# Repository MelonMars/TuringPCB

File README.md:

# Turing PCB

This is a PCB for a [Turing Machine](https://en.wikipedia.org/wiki/Turing_machine) that is made primarily using "simple" components, without using complex microchips or programmable stuff (as that would be cheating). It is designed to be programmed through the transition table being bridged by diodes (e.g. LEDs) in order to represent what is being done and how the machine should progress. It has both an automatic clock and the ability to step through it, to enable debugging programs or just run through them. It has 4 state bits and 8 tape bits. It ended up being much more complex than I thought at first, and took way longer than expected, but it was really enjoyable. It has 6 layers & 2 flood fills for both GND and VCC.

I made this project primarily for the fun of it. I've always found challenges with confounding variables fun and interesting, and believe that this is just sort of the next step in that regard, with Turing Machine's being fun proofs of concept and this being a very restricted form of it.

Bill of materials:
1x PCB (JLCPCB) -- $62.70

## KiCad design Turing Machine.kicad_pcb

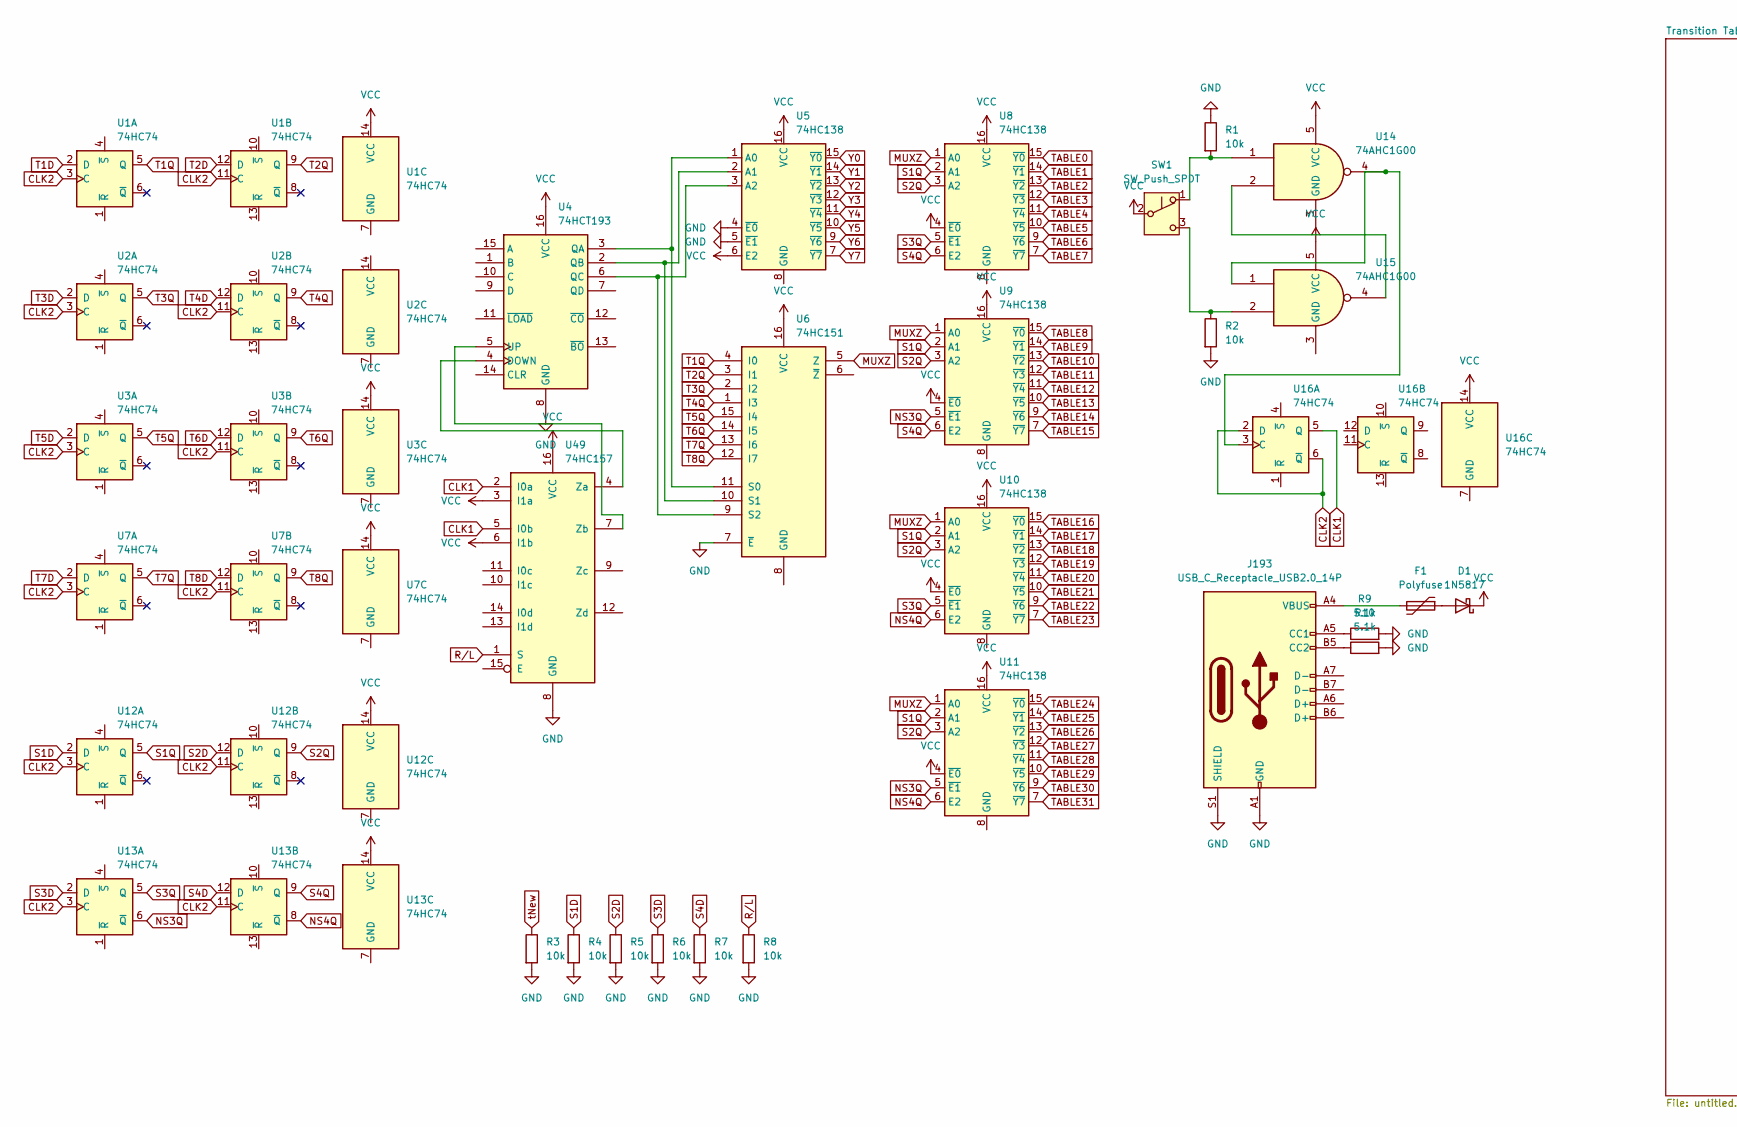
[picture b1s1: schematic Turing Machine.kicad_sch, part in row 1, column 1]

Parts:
D1: 1N5817; D_DO-41_SOD81_P10.16mm_Horizontal
F1: Polyfuse; Fuse_1812_4532Metric
J193: USB_C_Receptacle_USB2.0_14P; USB_C_Receptacle_GCT_USB4085
R1, R2, R3, R4, R5, R6, R7, R8: 10k; R_0603_1608Metric
R9, R10: 5.1k; R_0603_1608Metric
SW1: SW_Push_SPDT; Nidec_Copal_CAS-120A
U1, U2, U3, U7, U12, U13, U16: 74HC74; SOIC-14_3.9x8.7mm_P1.27mm
U4: 74HCT193; SOIC-16_3.9x9.9mm_P1.27mm
U5, U8, U9, U10, U11: 74HC138; SOIC-16_3.9x9.9mm_P1.27mm
U6: 74HC151; SOIC-16_3.9x9.9mm_P1.27mm
U14, U15: 74AHC1G00; SOT-23-5
U49: 74HC157; SOIC-16_3.9x9.9mm_P1.27mm

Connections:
CLK1: U16.5 (Q), U49.2 (I0a), U49.5 (I0b)
CLK2: U1.3 (C), U1.11 (C), U2.3 (C), U2.11 (C), U3.3 (C), U3.11 (C), U7.3 (C), U7.11 (C), U12.3 (C), U12.11 (C), U13.3 (C), U13.11 (C), U16.2 (D), U16.6 (~Q)
GND: J193.A1 (GND), J193.A12 (GND), J193.B1 (GND), J193.B12 (GND), J193.S1 (SHIELD), R1.1, R2.2, R3.2, R4.2, R5.2, R6.2, R7.2, R8.2, R9.2, R10.2, U4.8 (GND), U5.4 (~E0), U5.5 (~E1), U6.7 (~E), U49.8 (GND); also elsewhere on the board
MUXZ: U6.5 (Z), U8.1 (A0), U9.1 (A0), U10.1 (A0), U11.1 (A0)
NS3Q: U9.5 (~E1), U11.5 (~E1), U13.6 (~Q)
NS4Q: U10.6 (E2), U11.6 (E2), U13.8 (~Q)
unnamed: D1.2 (A), F1.1
unnamed: F1.2, J193.A4 (VBUS), J193.A9 (VBUS), J193.B4 (VBUS), J193.B9 (VBUS)
unnamed: J193.A5 (CC1), R9.1
unnamed: J193.B5 (CC2), R10.1
unnamed: R1.2, SW1.1 (A), U14.1
unnamed: R2.1, SW1.3 (C), U15.2
unnamed: U4.4 (DOWN), U49.4 (Za)
unnamed: U4.3 (QA), U5.1 (A0), U6.11 (S0)
unnamed: U4.2 (QB), U5.2 (A1), U6.10 (S1)
unnamed: U4.6 (QC), U5.3 (A2), U6.9 (S2)
unnamed: U4.5 (UP), U49.7 (Zb)
unnamed: U14.2, U15.4
unnamed: U14.4, U15.1, U16.3 (C)
R/L: R8.1, U49.1 (S); also elsewhere on the board
S1D: R4.1, U12.2 (D); also elsewhere on the board
S1Q: U8.2 (A1), U9.2 (A1), U10.2 (A1), U11.2 (A1), U12.5 (Q)
S2D: R5.1, U12.12 (D); also elsewhere on the board
S2Q: U8.3 (A2), U9.3 (A2), U10.3 (A2), U11.3 (A2), U12.9 (Q)
S3D: R6.1, U13.2 (D); also elsewhere on the board
S3Q: U8.5 (~E1), U10.5 (~E1), U13.5 (Q)
S4D: R7.1, U13.12 (D); also elsewhere on the board
S4Q: U8.6 (E2), U9.6 (E2), U13.9 (Q)
T1D: U1.2 (D); also elsewhere on the board
T1Q: U1.5 (Q), U6.4 (I0); also elsewhere on the board
T2D: U1.12 (D); also elsewhere on the board
T2Q: U1.9 (Q), U6.3 (I1); also elsewhere on the board
T3D: U2.2 (D); also elsewhere on the board
T3Q: U2.5 (Q), U6.2 (I2); also elsewhere on the board
T4D: U2.12 (D); also elsewhere on the board
T4Q: U2.9 (Q), U6.1 (I3); also elsewhere on the board
T5D: U3.2 (D); also elsewhere on the board
T5Q: U3.5 (Q), U6.15 (I4); also elsewhere on the board
T6D: U3.12 (D); also elsewhere on the board
T6Q: U3.9 (Q), U6.14 (I5); also elsewhere on the board
T7D: U7.2 (D); also elsewhere on the board
T7Q: U6.13 (I6), U7.5 (Q); also elsewhere on the board
T8D: U7.12 (D); also elsewhere on the board
T8Q: U6.12 (I7), U7.9 (Q); also elsewhere on the board
TABLE0: U8.15 (~Y0); also elsewhere on the board
TABLE1: U8.14 (~Y1); also elsewhere on the board
TABLE2: U8.13 (~Y2); also elsewhere on the board
TABLE3: U8.12 (~Y3); also elsewhere on the board
TABLE4: U8.11 (~Y4); also elsewhere on the board
TABLE5: U8.10 (~Y5); also elsewhere on the board
TABLE6: U8.9 (~Y6); also elsewhere on the board
TABLE7: U8.7 (~Y7); also elsewhere on the board
TABLE8: U9.15 (~Y0); also elsewhere on the board
TABLE9: U9.14 (~Y1); also elsewhere on the board
TABLE10: U9.13 (~Y2); also elsewhere on the board
TABLE11: U9.12 (~Y3); also elsewhere on the board
TABLE12: U9.11 (~Y4); also elsewhere on the board
TABLE13: U9.10 (~Y5); also elsewhere on the board
TABLE14: U9.9 (~Y6); also elsewhere on the board
TABLE15: U9.7 (~Y7); also elsewhere on the board
TABLE16: U10.15 (~Y0); also elsewhere on the board
TABLE17: U10.14 (~Y1); also elsewhere on the board
TABLE18: U10.13 (~Y2); also elsewhere on the board
TABLE19: U10.12 (~Y3); also elsewhere on the board
TABLE20: U10.11 (~Y4); also elsewhere on the board
TABLE21: U10.10 (~Y5); also elsewhere on the board
TABLE22: U10.9 (~Y6); also elsewhere on the board
TABLE23: U10.7 (~Y7); also elsewhere on the board
TABLE24: U11.15 (~Y0); also elsewhere on the board
TABLE25: U11.14 (~Y1); also elsewhere on the board
TABLE26: U11.13 (~Y2); also elsewhere on the board
TABLE27: U11.12 (~Y3); also elsewhere on the board
TABLE28: U11.11 (~Y4); also elsewhere on the board
TABLE29: U11.10 (~Y5); also elsewhere on the board
TABLE30: U11.9 (~Y6); also elsewhere on the board
TABLE31: U11.7 (~Y7); also elsewhere on the board
VCC: D1.1 (K), SW1.2 (B), U1.14 (VCC), U3.14 (VCC), U4.16 (VCC), U5.6 (E2), U5.16 (VCC), U6.16 (VCC), U7.14 (VCC), U8.4 (~E0), U8.16 (VCC), U9.4 (~E0), U9.16 (VCC), U10.4 (~E0), U10.16 (VCC), U11.4 (~E0), U11.16 (VCC), U12.14 (VCC), U13.14 (VCC), U14.5 (VCC), U15.5 (VCC), U16.14 (VCC), U49.3 (I1a), U49.6 (I1b), U49.16 (VCC); also elsewhere on the board
Y0: U5.15 (~Y0); also elsewhere on the board
Y1: U5.14 (~Y1); also elsewhere on the board
Y2: U5.13 (~Y2); also elsewhere on the board
Y3: U5.12 (~Y3); also elsewhere on the board
Y4: U5.11 (~Y4); also elsewhere on the board
Y5: U5.10 (~Y5); also elsewhere on the board
Y6: U5.9 (~Y6); also elsewhere on the board
Y7: U5.7 (~Y7); also elsewhere on the board
tNew: R3.1; also elsewhere on the board

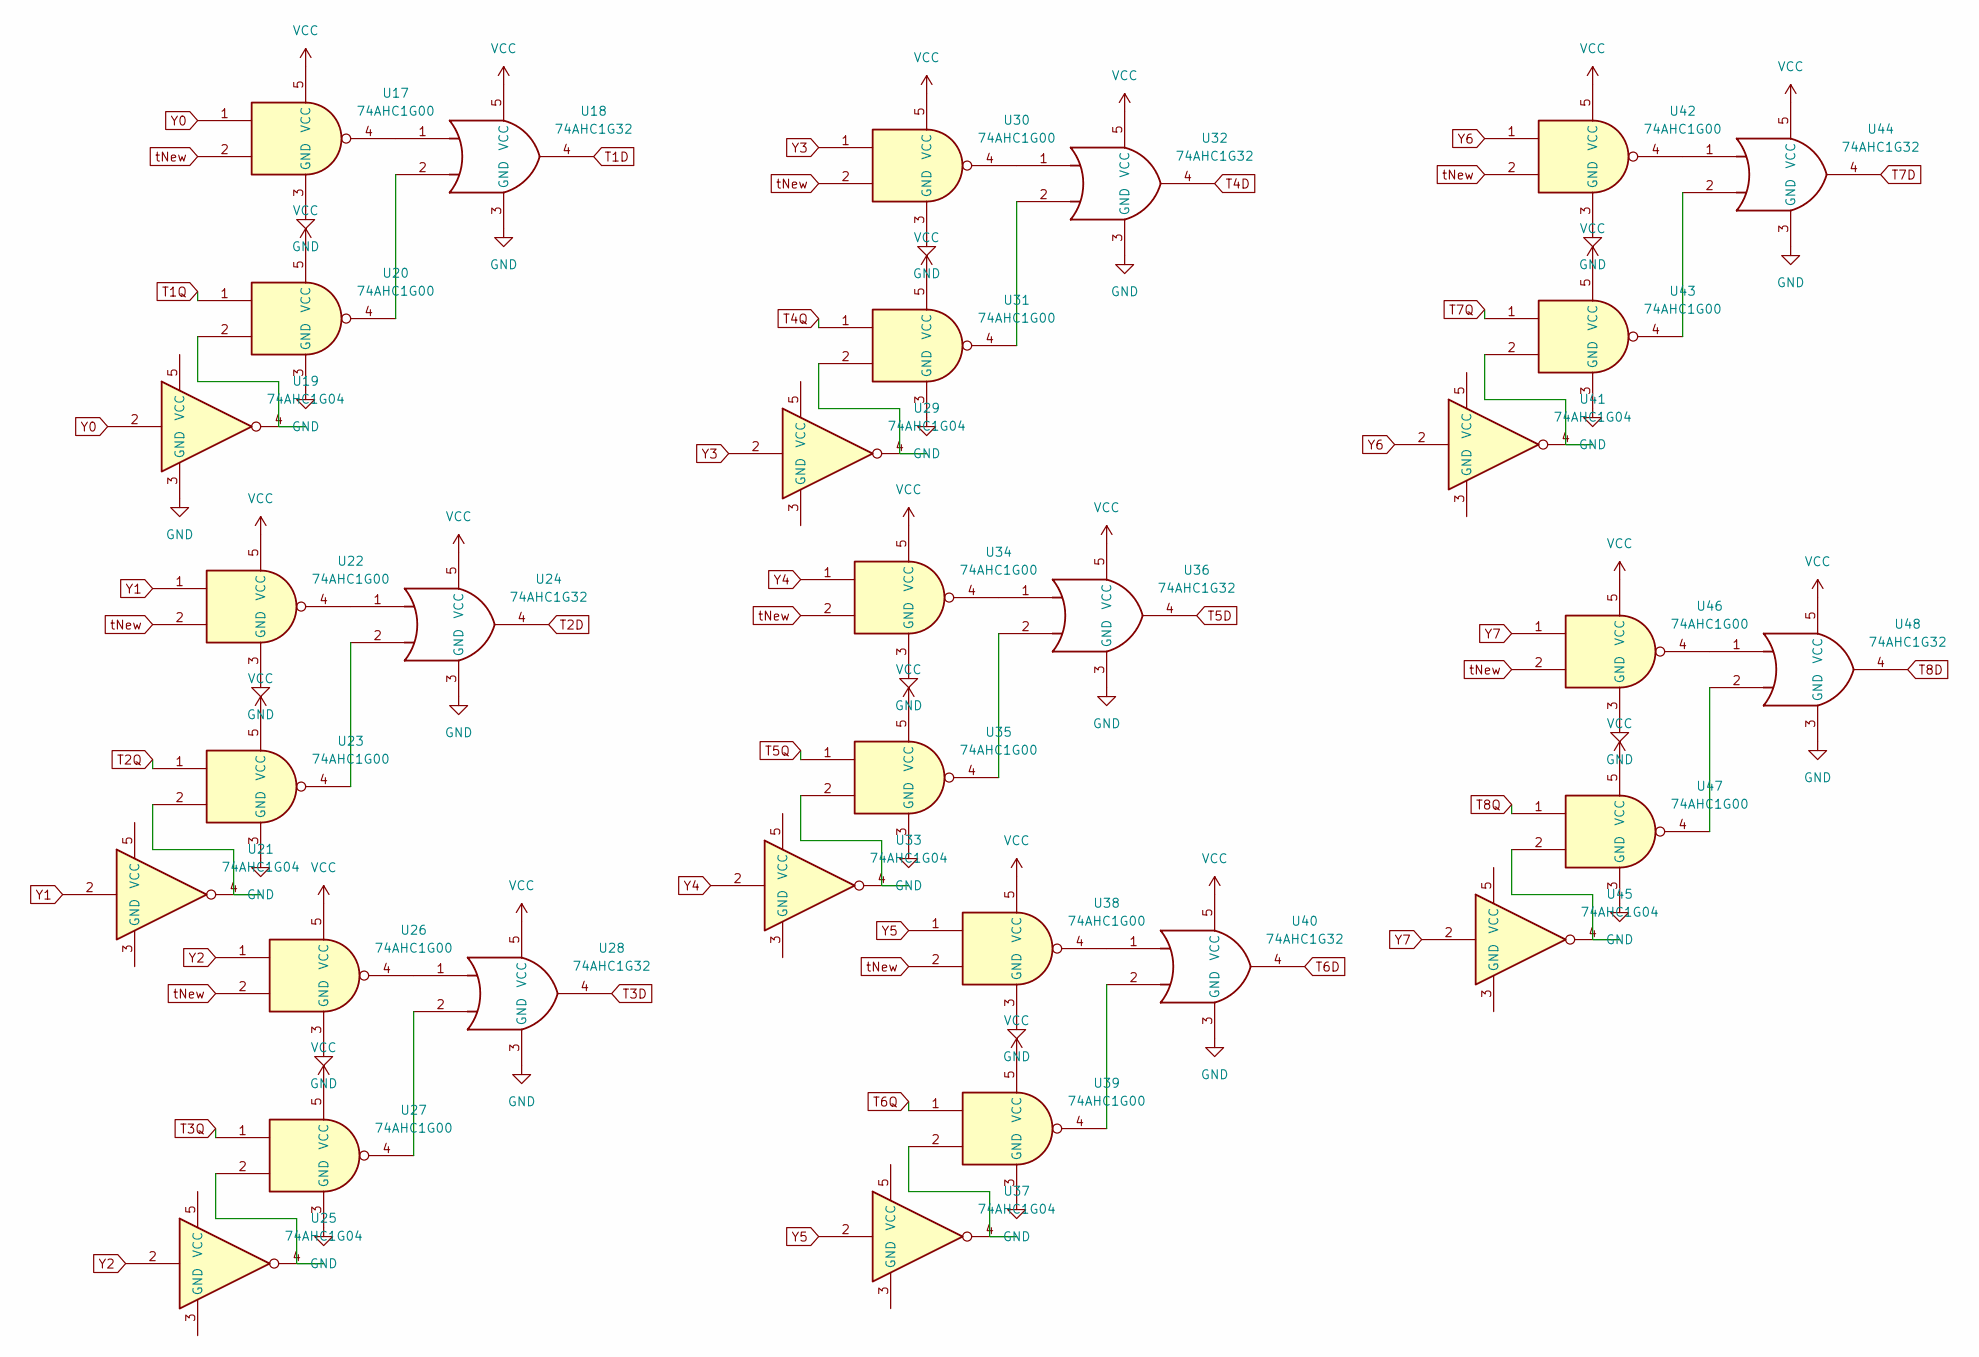
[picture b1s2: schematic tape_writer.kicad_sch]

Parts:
U17, U20, U22, U23, U26, U27, U30, U31, U34, U35, U38, U39, U42, U43, U46, U47: 74AHC1G00; SOT-23-5
U18, U24, U28, U32, U36, U40, U44, U48: 74AHC1G32; SOT-23-5
U19, U21, U25, U29, U33, U37, U41, U45: 74AHC1G04; SOT-23-5

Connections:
GND: U17.3 (GND), U18.3 (GND), U19.3 (GND), U20.3 (GND), U22.3 (GND), U23.3 (GND), U24.3 (GND), U26.3 (GND), U27.3 (GND), U28.3 (GND), U30.3 (GND), U31.3 (GND), U32.3 (GND), U34.3 (GND), U35.3 (GND), U36.3 (GND), U38.3 (GND), U39.3 (GND), U40.3 (GND), U42.3 (GND), U43.3 (GND), U44.3 (GND), U46.3 (GND), U47.3 (GND), U48.3 (GND); also elsewhere on the board
unnamed: U17.4, U18.1
unnamed: U18.2, U20.4
unnamed: U19.4, U20.2
unnamed: U21.4, U23.2
unnamed: U22.4, U24.1
unnamed: U23.4, U24.2
unnamed: U25.4, U27.2
unnamed: U26.4, U28.1
unnamed: U27.4, U28.2
unnamed: U29.4, U31.2
unnamed: U30.4, U32.1
unnamed: U31.4, U32.2
unnamed: U33.4, U35.2
unnamed: U34.4, U36.1
unnamed: U35.4, U36.2
unnamed: U37.4, U39.2
unnamed: U38.4, U40.1
unnamed: U39.4, U40.2
unnamed: U41.4, U43.2
unnamed: U42.4, U44.1
unnamed: U43.4, U44.2
unnamed: U45.4, U47.2
unnamed: U46.4, U48.1
unnamed: U47.4, U48.2
T1D: U18.4; also elsewhere on the board
T1Q: U20.1; also elsewhere on the board
T2D: U24.4; also elsewhere on the board
T2Q: U23.1; also elsewhere on the board
T3D: U28.4; also elsewhere on the board
T3Q: U27.1; also elsewhere on the board
T4D: U32.4; also elsewhere on the board
T4Q: U31.1; also elsewhere on the board
T5D: U36.4; also elsewhere on the board
T5Q: U35.1; also elsewhere on the board
T6D: U40.4; also elsewhere on the board
T6Q: U39.1; also elsewhere on the board
T7D: U44.4; also elsewhere on the board
T7Q: U43.1; also elsewhere on the board
T8D: U48.4; also elsewhere on the board
T8Q: U47.1; also elsewhere on the board
VCC: U17.5 (VCC), U18.5 (VCC), U20.5 (VCC), U22.5 (VCC), U23.5 (VCC), U24.5 (VCC), U26.5 (VCC), U27.5 (VCC), U28.5 (VCC), U30.5 (VCC), U31.5 (VCC), U32.5 (VCC), U34.5 (VCC), U35.5 (VCC), U36.5 (VCC), U38.5 (VCC), U39.5 (VCC), U40.5 (VCC), U42.5 (VCC), U43.5 (VCC), U44.5 (VCC), U46.5 (VCC), U47.5 (VCC), U48.5 (VCC); also elsewhere on the board
Y0: U17.1, U19.2; also elsewhere on the board
Y1: U21.2, U22.1; also elsewhere on the board
Y2: U25.2, U26.1; also elsewhere on the board
Y3: U29.2, U30.1; also elsewhere on the board
Y4: U33.2, U34.1; also elsewhere on the board
Y5: U37.2, U38.1; also elsewhere on the board
Y6: U41.2, U42.1; also elsewhere on the board
Y7: U45.2, U46.1; also elsewhere on the board
tNew: U17.2, U22.2, U26.2, U30.2, U34.2, U38.2, U42.2, U46.2; also elsewhere on the board

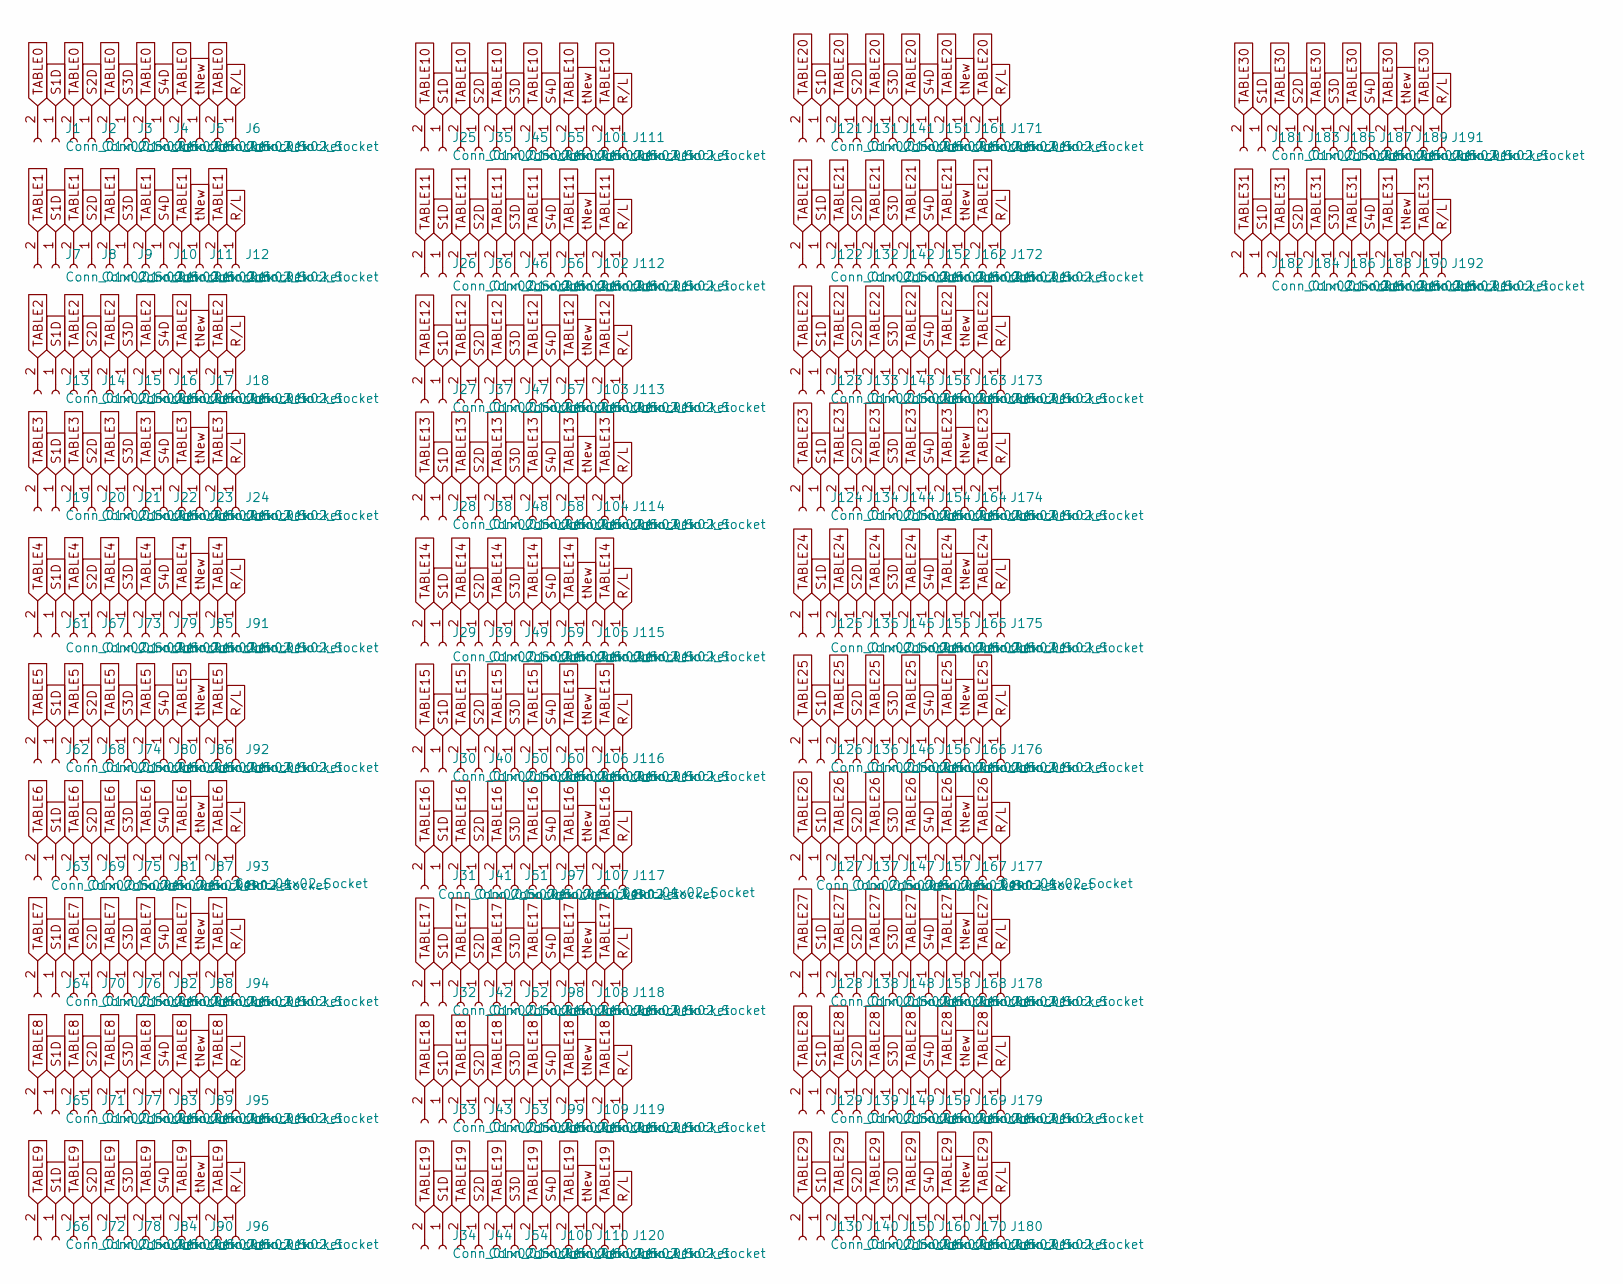
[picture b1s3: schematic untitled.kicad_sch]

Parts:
J1, J2, J3, J4, J5, J6, J7, J8, J9, J10, J11, J12, J13, J14, J15, J16, J17, J18, J19, J20, J21, J22, J23, J24, J25, J26, J27, J28, J29, J30, J31, J32, J33, J34, J35, J36, J37, J38, J39, J40, J41, J42, J43, J44, J45, J46, J47, J48, J49, J50, J51, J52, J53, J54, J55, J56, J57, J58, J59, J60, J61, J62, J63, J64, J65, J66, J67, J68, J69, J70, J71, J72, J73, J74, J75, J76, J77, J78, J79, J80, J81, J82, J83, J84, J85, J86, J87, J88, J89, J90, J91, J92, J93, J94, J95, J96, J97, J98, J99, J100, J101, J102, J103, J104, J105, J106, J107, J108, J109, J110, J111, J112, J113, J114, J115, J116, J117, J118, J119, J120, J121, J122, J123, J124, J125, J126, J127, J128, J129, J130, J131, J132, J133, J134, J135, J136, J137, J138, J139, J140, J141, J142, J143, J144, J145, J146, J147, J148, J149, J150, J151, J152, J153, J154, J155, J156, J157, J158, J159, J160, J161, J162, J163, J164, J165, J166, J167, J168, J169, J170, J171, J172, J173, J174, J175, J176, J177, J178, J179, J180, J181, J182, J183, J184, J185, J186, J187, J188, J189, J190, J191, J192: Conn_01x02_Socket; PinSocket_1x02_P2.54mm_Vertical

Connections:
R/L: J6.1, J12.1, J18.1, J24.1, J91.1, J92.1, J93.1, J94.1, J95.1, J96.1, J111.1, J112.1, J113.1, J114.1, J115.1, J116.1, J117.1, J118.1, J119.1, J120.1, J171.1, J172.1, J173.1, J174.1, J175.1, J176.1, J177.1, J178.1, J179.1, J180.1, J191.1, J192.1; also elsewhere on the board
S1D: J1.1, J7.1, J13.1, J19.1, J25.1, J26.1, J27.1, J28.1, J29.1, J30.1, J31.1, J32.1, J33.1, J34.1, J61.1, J62.1, J63.1, J64.1, J65.1, J66.1, J121.1, J122.1, J123.1, J124.1, J125.1, J126.1, J127.1, J128.1, J129.1, J130.1, J181.1, J182.1; also elsewhere on the board
S2D: J2.1, J8.1, J14.1, J20.1, J35.1, J36.1, J37.1, J38.1, J39.1, J40.1, J41.1, J42.1, J43.1, J44.1, J67.1, J68.1, J69.1, J70.1, J71.1, J72.1, J131.1, J132.1, J133.1, J134.1, J135.1, J136.1, J137.1, J138.1, J139.1, J140.1, J183.1, J184.1; also elsewhere on the board
S3D: J3.1, J9.1, J15.1, J21.1, J45.1, J46.1, J47.1, J48.1, J49.1, J50.1, J51.1, J52.1, J53.1, J54.1, J73.1, J74.1, J75.1, J76.1, J77.1, J78.1, J141.1, J142.1, J143.1, J144.1, J145.1, J146.1, J147.1, J148.1, J149.1, J150.1, J185.1, J186.1; also elsewhere on the board
S4D: J4.1, J10.1, J16.1, J22.1, J55.1, J56.1, J57.1, J58.1, J59.1, J60.1, J79.1, J80.1, J81.1, J82.1, J83.1, J84.1, J97.1, J98.1, J99.1, J100.1, J151.1, J152.1, J153.1, J154.1, J155.1, J156.1, J157.1, J158.1, J159.1, J160.1, J187.1, J188.1; also elsewhere on the board
TABLE0: J1.2, J2.2, J3.2, J4.2, J5.2, J6.2; also elsewhere on the board
TABLE1: J7.2, J8.2, J9.2, J10.2, J11.2, J12.2; also elsewhere on the board
TABLE2: J13.2, J14.2, J15.2, J16.2, J17.2, J18.2; also elsewhere on the board
TABLE3: J19.2, J20.2, J21.2, J22.2, J23.2, J24.2; also elsewhere on the board
TABLE4: J61.2, J67.2, J73.2, J79.2, J85.2, J91.2; also elsewhere on the board
TABLE5: J62.2, J68.2, J74.2, J80.2, J86.2, J92.2; also elsewhere on the board
TABLE6: J63.2, J69.2, J75.2, J81.2, J87.2, J93.2; also elsewhere on the board
TABLE7: J64.2, J70.2, J76.2, J82.2, J88.2, J94.2; also elsewhere on the board
TABLE8: J65.2, J71.2, J77.2, J83.2, J89.2, J95.2; also elsewhere on the board
TABLE9: J66.2, J72.2, J78.2, J84.2, J90.2, J96.2; also elsewhere on the board
TABLE10: J25.2, J35.2, J45.2, J55.2, J101.2, J111.2; also elsewhere on the board
TABLE11: J26.2, J36.2, J46.2, J56.2, J102.2, J112.2; also elsewhere on the board
TABLE12: J27.2, J37.2, J47.2, J57.2, J103.2, J113.2; also elsewhere on the board
TABLE13: J28.2, J38.2, J48.2, J58.2, J104.2, J114.2; also elsewhere on the board
TABLE14: J29.2, J39.2, J49.2, J59.2, J105.2, J115.2; also elsewhere on the board
TABLE15: J30.2, J40.2, J50.2, J60.2, J106.2, J116.2; also elsewhere on the board
TABLE16: J31.2, J41.2, J51.2, J97.2, J107.2, J117.2; also elsewhere on the board
TABLE17: J32.2, J42.2, J52.2, J98.2, J108.2, J118.2; also elsewhere on the board
TABLE18: J33.2, J43.2, J53.2, J99.2, J109.2, J119.2; also elsewhere on the board
TABLE19: J34.2, J44.2, J54.2, J100.2, J110.2, J120.2; also elsewhere on the board
TABLE20: J121.2, J131.2, J141.2, J151.2, J161.2, J171.2; also elsewhere on the board
TABLE21: J122.2, J132.2, J142.2, J152.2, J162.2, J172.2; also elsewhere on the board
TABLE22: J123.2, J133.2, J143.2, J153.2, J163.2, J173.2; also elsewhere on the board
TABLE23: J124.2, J134.2, J144.2, J154.2, J164.2, J174.2; also elsewhere on the board
TABLE24: J125.2, J135.2, J145.2, J155.2, J165.2, J175.2; also elsewhere on the board
TABLE25: J126.2, J136.2, J146.2, J156.2, J166.2, J176.2; also elsewhere on the board
TABLE26: J127.2, J137.2, J147.2, J157.2, J167.2, J177.2; also elsewhere on the board
TABLE27: J128.2, J138.2, J148.2, J158.2, J168.2, J178.2; also elsewhere on the board
TABLE28: J129.2, J139.2, J149.2, J159.2, J169.2, J179.2; also elsewhere on the board
TABLE29: J130.2, J140.2, J150.2, J160.2, J170.2, J180.2; also elsewhere on the board
TABLE30: J181.2, J183.2, J185.2, J187.2, J189.2, J191.2; also elsewhere on the board
TABLE31: J182.2, J184.2, J186.2, J188.2, J190.2, J192.2; also elsewhere on the board
tNew: J5.1, J11.1, J17.1, J23.1, J85.1, J86.1, J87.1, J88.1, J89.1, J90.1, J101.1, J102.1, J103.1, J104.1, J105.1, J106.1, J107.1, J108.1, J109.1, J110.1, J161.1, J162.1, J163.1, J164.1, J165.1, J166.1, J167.1, J168.1, J169.1, J170.1, J189.1, J190.1; also elsewhere on the board

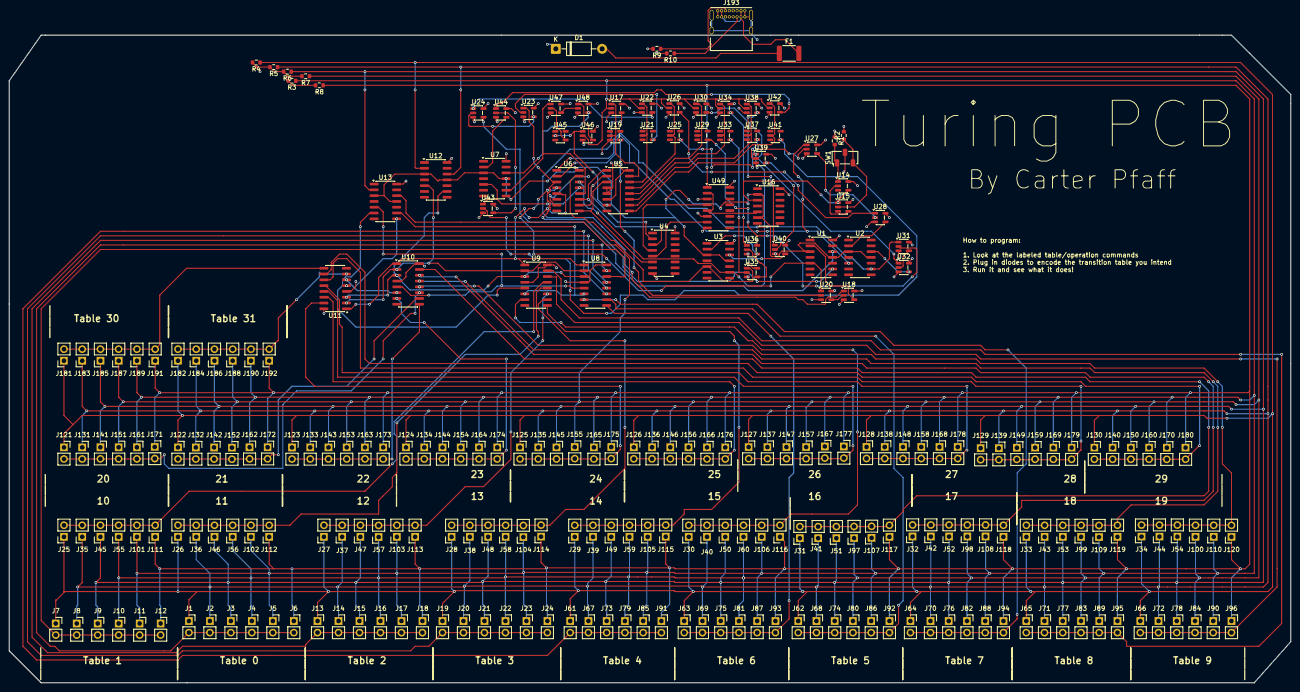
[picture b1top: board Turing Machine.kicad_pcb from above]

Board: 4 copper layers, 281.0 x 142.0 mm, 255 parts (0 on the bottom side), 110 nets.

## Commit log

2026-05-13 readme update
2026-05-16 Fixed according to notes
2026-05-28 Move to OpenSauce
2026-06-21 Update unconnected
2026-06-21 Fix DRC
2026-06-23 Respond to comments
